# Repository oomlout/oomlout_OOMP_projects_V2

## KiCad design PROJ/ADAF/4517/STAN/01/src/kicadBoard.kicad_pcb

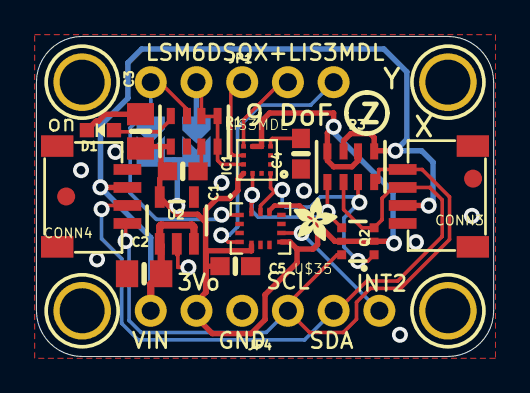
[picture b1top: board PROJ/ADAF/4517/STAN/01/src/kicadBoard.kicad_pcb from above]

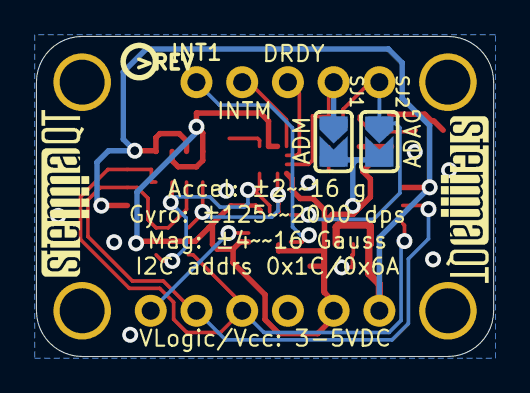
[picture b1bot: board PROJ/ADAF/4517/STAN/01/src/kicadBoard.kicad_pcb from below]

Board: 2 copper layers, 25.4 x 17.8 mm, 28 parts (5 on the bottom side), 15 nets.

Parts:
C1, C4: 0.1uF; 0603-NO
C2, C3: 10uF; 0805-NO
C5: 1uF; 0603-NO
CONN3, CONN4: STEMMA_I2C_QT; JST_SH4
D1: GREEN; CHIPLED_0603_NOOUTLINE
FID3, FID4: FIDUCIAL_1MM
IC1: LIS3MDL; LGA12_2X2MM
JP1: 1X05_ROUND_70
JP4: 1X06_ROUND_70
Q2: BSS138; SOT363
R1, R3: 10K; RESPACK_4X0603
SJ1, SJ2: SOLDERJUMPER_ARROW_NOPASTE
U2: AP2112K-3.3; SOT23-5
U$1, U$17, U$19, U$21: MOUNTINGHOLE2.5; MOUNTINGHOLE_2.5_PLATED
U$20: ADAFRUIT_2.5MM
U$25: PCBFEAT-REV-040
U$30, U$31: STEMMAQT
U$35: LSM6DSOX; LGA-14L

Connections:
3.3V: C1.1, C3.1, C5.1, IC1.5, IC1.6, IC1.10, JP4.2, Q2.2, Q2.5, R1.1, R3.2, R3.4, SJ1.2, SJ2.2, U2.5, U$35.5, U$35.8, U$35.12
ADAG: JP1.1, R1.7, SJ2.1, U$35.1
ADM: IC1.9, JP1.2, R1.4, R1.5, R1.6, SJ1.1
CAP: C4.1, IC1.4
DRDY: IC1.8, JP1.3
GND: C1.2, C2.2, C3.2, C4.2, C5.2, CONN3.1, CONN3.MT1, CONN3.MT2, CONN4.1, CONN4.MT1, CONN4.MT2, D1.C, IC1.2, IC1.3, IC1.12, JP4.3, R1.2, R1.3, U2.2, U$35.6, U$35.7
INT1: JP1.5, U$35.4
INT2: JP4.6, U$35.9
INTM: IC1.7, JP1.4
unnamed: D1.A, R1.8
SCL: CONN3.4, CONN4.4, JP4.4, Q2.6, R3.8
SCL_3V: IC1.1, Q2.1, R3.7, U$35.13
SDA: CONN3.3, CONN4.3, JP4.5, Q2.3, R3.6
SDA_3V: IC1.11, Q2.4, R3.5, U$35.14
VCC: C2.1, CONN3.2, CONN4.2, JP4.1, R3.1, R3.3, U2.1, U2.3

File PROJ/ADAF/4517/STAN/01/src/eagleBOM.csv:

"Part";"Value";"Device";"Package";"Description";"BOM";
"C1";"0.1uF";"CAP_CERAMIC0603_NO";"0603-NO";"Ceramic Capacitors";"";
"C2";"10uF";"CAP_CERAMIC0805-NOOUTLINE";"0805-NO";"Ceramic Capacitors";"";
"C3";"10uF";"CAP_CERAMIC0805-NOOUTLINE";"0805-NO";"Ceramic Capacitors";"";
"C4";"0.1uF";"CAP_CERAMIC0603_NO";"0603-NO";"Ceramic Capacitors";"";
"C5";"1uF";"CAP_CERAMIC0603_NO";"0603-NO";"Ceramic Capacitors";"";
"CONN3";"STEMMA_I2C_QT";"STEMMA_I2C_QT";"JST_SH4";"";"";
"CONN4";"STEMMA_I2C_QT";"STEMMA_I2C_QT";"JST_SH4";"";"";
"D1";"GREEN";"LED0603_NOOUTLINE";"CHIPLED_0603_NOOUTLINE";"LED";"";
"FID3";"FIDUCIAL_1MM";"FIDUCIAL_1MM";"FIDUCIAL_1MM";"Fiducial Alignment Points";"EXCLUDE";
"FID4";"FIDUCIAL_1MM";"FIDUCIAL_1MM";"FIDUCIAL_1MM";"Fiducial Alignment Points";"EXCLUDE";
"IC1";"LIS3MDL";"LIS3MDL";"LGA12_2X2MM";"Digital output magnetic sensor. ultra-low-power, high-performance 3-axis magnetometer";"";
"JP1";"";"HEADER-1X570MIL";"1X05_ROUND_70";"PIN HEADER";"";
"JP4";"";"HEADER-1X670MIL";"1X06_ROUND_70";"PIN HEADER";"";
"Q2";"BSS138";"MOSFET-N_DUAL";"SOT363";"Dual N-Channel MOSFET";"";
"R1";"10K";"RESISTOR_4PACK";"RESPACK_4X0603";"Resistor Packs (4 resistors)";"";
"R3";"10K";"RESISTOR_4PACK";"RESPACK_4X0603";"Resistor Packs (4 resistors)";"";
"SJ1";"";"SOLDERJUMPER";"SOLDERJUMPER_ARROW_NOPASTE";"SMD Solder JUMPER";"EXCLUDE";
"SJ2";"";"SOLDERJUMPER";"SOLDERJUMPER_ARROW_NOPASTE";"SMD Solder JUMPER";"EXCLUDE";
"U$1";"MOUNTINGHOLE2.5";"MOUNTINGHOLE2.5";"MOUNTINGHOLE_2.5_PLATED";"Mounting Hole";"EXCLUDE";
"U$17";"MOUNTINGHOLE2.5";"MOUNTINGHOLE2.5";"MOUNTINGHOLE_2.5_PLATED";"Mounting Hole";"EXCLUDE";
"U$19";"MOUNTINGHOLE2.5";"MOUNTINGHOLE2.5";"MOUNTINGHOLE_2.5_PLATED";"Mounting Hole";"EXCLUDE";
"U$21";"MOUNTINGHOLE2.5";"MOUNTINGHOLE2.5";"MOUNTINGHOLE_2.5_PLATED";"Mounting Hole";"EXCLUDE";
"U$35";"LSM6DSOX";"LSM6DSOX";"LGA-14L";"";"";
"U2";"AP2112K-3.3";"VREG_SOT23-5";"SOT23-5";"SOT23-5 Fixed Voltage Regulators";"";

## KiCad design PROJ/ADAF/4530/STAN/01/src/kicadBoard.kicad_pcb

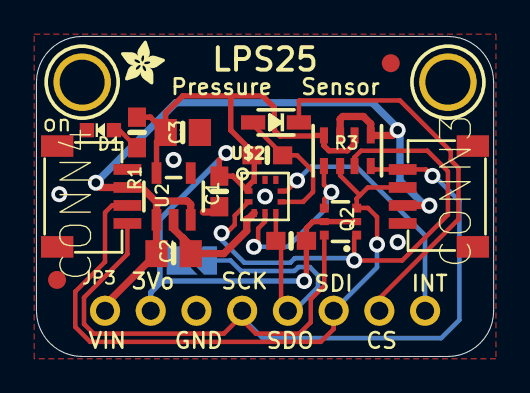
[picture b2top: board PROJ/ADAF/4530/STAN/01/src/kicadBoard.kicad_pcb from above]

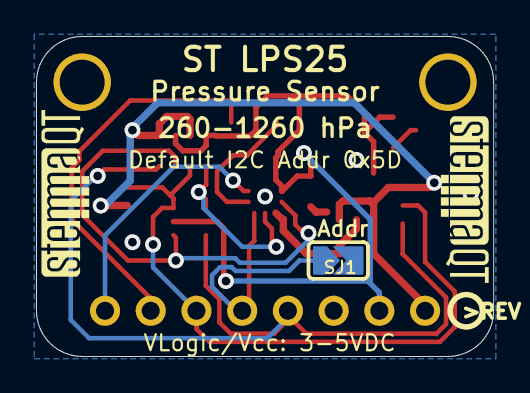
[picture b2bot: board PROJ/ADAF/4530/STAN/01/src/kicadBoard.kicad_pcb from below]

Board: 2 copper layers, 25.4 x 17.8 mm, 24 parts (4 on the bottom side), 12 nets.

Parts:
C1: 0.1uF; 0603-NO
C2, C3: 10uF; 0805-NO
CONN3, CONN4: STEMMA_I2C_QT; JST_SH4
D1: GREEN; CHIPLED_0603_NOOUTLINE
D2: 1N4148; SOD-323
FID3, FID4: FIDUCIAL_1MM
JP3: 1X08_ROUND
Q2: BSS138; SOT363
R1, R4, R5: 10K; 0603-NO
R3: 10K; RESPACK_4X0603
SJ1: SOLDERJUMPER_ARROW_NOPASTE
U2: AP2112K-3.3; SOT23-5
U$1, U$17: MOUNTINGHOLE2.5; MOUNTINGHOLE_2.5_PLATED
U$2: LPS2X_LPS25; HLGA-10L
U$4: ADAFRUIT_2.5MM
U$25: PCBFEAT-REV-040
U$30, U$31: STEMMAQT

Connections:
3.3V: C1.1, C3.1, JP3.2, Q2.2, Q2.5, R1.1, R3.2, R3.4, R4.2, R5.2, U2.5, U$2.1, U$2.10
CS: D2.C, JP3.7
CS_3V: D2.A, R5.1, U$2.6
GND: C1.2, C2.2, C3.2, CONN3.1, CONN4.1, D1.C, JP3.3, SJ1.2, U2.2, U$2.3, U$2.8, U$2.9
INT: JP3.8, U$2.7
unnamed: D1.A, R1.2
SCK/SCL: CONN3.4, CONN4.4, JP3.4, Q2.6, R3.8
SCK_3V: Q2.1, R3.7, U$2.2
SDI/SDA: CONN3.3, CONN4.3, JP3.6, Q2.3, R3.6
SDI_3V: Q2.4, R3.5, U$2.4
SDO/ADR: JP3.5, R4.1, SJ1.1, U$2.5
VCC: C2.1, CONN3.2, CONN4.2, JP3.1, R3.1, R3.3, U2.1, U2.3

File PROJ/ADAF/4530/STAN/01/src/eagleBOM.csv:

"Part";"Value";"Device";"Package";"Description";"BOM";
"C1";"0.1uF";"CAP_CERAMIC0603_NO";"0603-NO";"Ceramic Capacitors";"";
"C2";"10uF";"CAP_CERAMIC0805-NOOUTLINE";"0805-NO";"Ceramic Capacitors";"";
"C3";"10uF";"CAP_CERAMIC0805-NOOUTLINE";"0805-NO";"Ceramic Capacitors";"";
"CONN3";"STEMMA_I2C_QT";"STEMMA_I2C_QT";"JST_SH4";"";"";
"CONN4";"STEMMA_I2C_QT";"STEMMA_I2C_QT";"JST_SH4";"";"";
"D1";"GREEN";"LED0603_NOOUTLINE";"CHIPLED_0603_NOOUTLINE";"LED";"";
"D2";"1N4148";"DIODESOD-323";"SOD-323";"Diode";"";
"FID3";"FIDUCIAL_1MM";"FIDUCIAL_1MM";"FIDUCIAL_1MM";"Fiducial Alignment Points";"EXCLUDE";
"FID4";"FIDUCIAL_1MM";"FIDUCIAL_1MM";"FIDUCIAL_1MM";"Fiducial Alignment Points";"EXCLUDE";
"JP3";"";"HEADER-1X8ROUND";"1X08_ROUND";"PIN HEADER";"";
"Q2";"BSS138";"MOSFET-N_DUAL";"SOT363";"Dual N-Channel MOSFET";"";
"R1";"10K";"RESISTOR_0603_NOOUT";"0603-NO";"Resistors";"";
"R3";"10K";"RESISTOR_4PACK";"RESPACK_4X0603";"Resistor Packs (4 resistors)";"";
"R4";"10K";"RESISTOR_0603_NOOUT";"0603-NO";"Resistors";"";
"R5";"10K";"RESISTOR_0603_NOOUT";"0603-NO";"Resistors";"";
"SJ1";"";"SOLDERJUMPER";"SOLDERJUMPER_ARROW_NOPASTE";"SMD Solder JUMPER";"EXCLUDE";
"U$1";"MOUNTINGHOLE2.5";"MOUNTINGHOLE2.5";"MOUNTINGHOLE_2.5_PLATED";"Mounting Hole";"EXCLUDE";
"U$2";"LPS2X_LPS25";"LPS2X_LPS25";"HLGA-10L";"";"";
"U$17";"MOUNTINGHOLE2.5";"MOUNTINGHOLE2.5";"MOUNTINGHOLE_2.5_PLATED";"Mounting Hole";"EXCLUDE";
"U2";"AP2112K-3.3";"VREG_SOT23-5";"SOT23-5";"SOT23-5 Fixed Voltage Regulators";"";

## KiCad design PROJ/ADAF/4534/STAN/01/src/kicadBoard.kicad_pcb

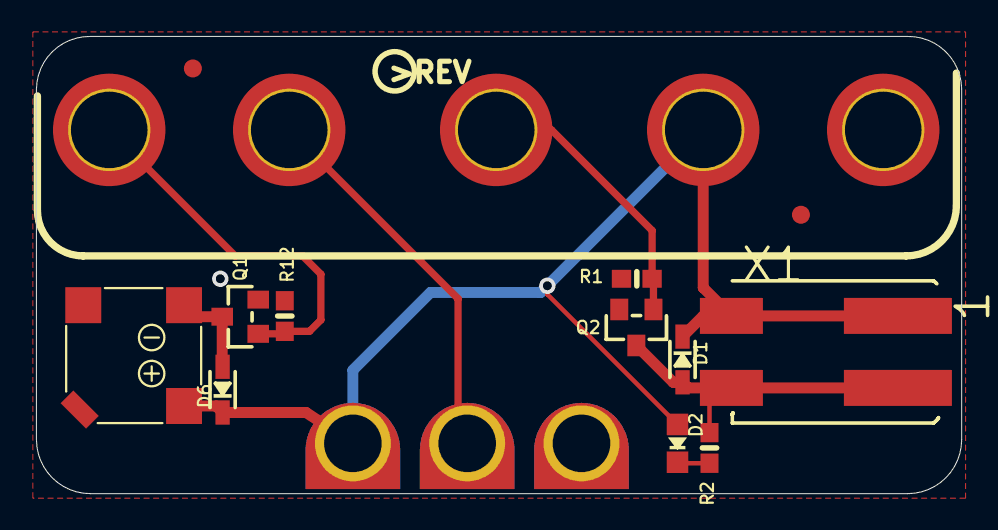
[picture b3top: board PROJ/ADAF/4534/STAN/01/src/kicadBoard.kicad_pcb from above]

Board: 2 copper layers, 51.4 x 25.4 mm, 19 parts (1 on the bottom side), 8 nets.

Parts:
D1, D6: 1N4148; SOD-323
D2: red; CHIPLED_0805_NOOUTLINE
FID1, FID2: FIDUCIAL_1MM
MB2: MICROBIT_5PIN; MICROBIT_5SMTNUT
Q1, Q2: BSS138; SOT23-WIDE
R1, R12: 10K; 0603-NO
R2: 1K; 0603-NO
SP1: SPEAKER_7.5MM; BUZZER_SMT_7.5MM
TP1, TP2, TP3: SEWTAPPCB_ALLIGATOR; PCB_ALLI
U$4: BONSAI_BOT
U$5: BONSAI_TOP
U$10: PCBFEAT-REV-056
X1: 2060-402/998-404; P-2060-402_998-404

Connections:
3.3V: D1.C, D2.A, D6.C, MB2.3V, SP1.+, TP1.P$1, X1.L1.1, X1.L1.2
GND: MB2.GND, Q1.2, Q2.2, R1.2, R12.2, TP3.P$1
unnamed: D1.A, Q2.3, R2.1, X1.L2.1, X1.L2.2
unnamed: D2.C, R2.2
unnamed: D6.A, Q1.3, SP1.-
P0: MB2.P0, Q1.1, R12.1
P1: MB2.P1, TP2.P$1
P2: MB2.P2, Q2.1, R1.1

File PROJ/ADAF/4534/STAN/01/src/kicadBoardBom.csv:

"Id";"Designator";"Package";"Quantity";"Designation";"Supplier and ref";
1;"D2";"CHIPLED_0805_NOOUTLINE";1;"red";;;
2;"FID1,FID2";"FIDUCIAL_1MM";2;"FIDUCIAL_1MM";;;
3;"Q2,Q1";"SOT23-WIDE";2;"BSS138";;;
4;"SP1";"BUZZER_SMT_7.5MM";1;"SPEAKER_7.5MM";;;
5;"TP3,TP1,TP2";"PCB_ALLI";3;"SEWTAPPCB_ALLIGATOR";;;
6;"R1,R12";"0603-NO";2;"10K";;;
7;"U$5";"BONSAI_TOP";1;"";;;
8;"D1,D6";"SOD-323";2;"1N4148";;;
9;"MB2";"MICROBIT_5SMTNUT";1;"MICROBIT_5PIN";;;
10;"X1";"P-2060-402_998-404";1;"2060-402/998-404";;;
11;"R2";"0603-NO";1;"1K";;;
12;"U$10";"PCBFEAT-REV-056";1;"";;;
13;"U$4";"BONSAI_BOT";1;"";;;

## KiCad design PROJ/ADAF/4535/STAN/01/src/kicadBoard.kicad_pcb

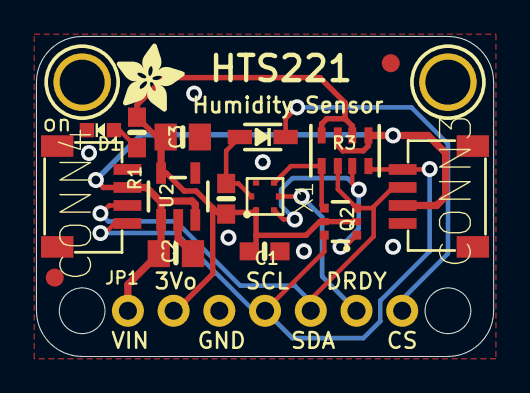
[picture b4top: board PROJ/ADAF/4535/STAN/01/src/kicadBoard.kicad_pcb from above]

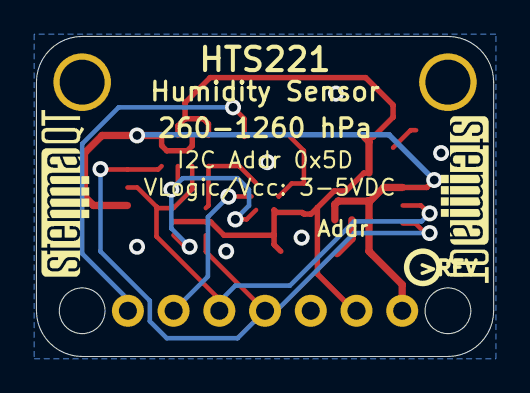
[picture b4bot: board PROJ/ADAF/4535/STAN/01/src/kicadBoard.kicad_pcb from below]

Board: 2 copper layers, 25.4 x 17.8 mm, 24 parts (3 on the bottom side), 11 nets.

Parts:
@HOLE0, @HOLE1: (no value)
C1: 0.1uF; 0603-NO
C2, C3: 10uF; 0805-NO
CONN3, CONN4: STEMMA_I2C_QT; JST_SH4
D1: GREEN; CHIPLED_0603_NOOUTLINE
D2: 1N4148; SOD-323
FID3, FID4: FIDUCIAL_1MM
JP1: 1X07_ROUND_70
Q2: BSS138; SOT363
R1, R5: 10K; 0603-NO
R3: 10K; RESPACK_4X0603
U2: AP2112K-3.3; SOT23-5
U$1, U$17: MOUNTINGHOLE2.5; MOUNTINGHOLE_2.5_PLATED
U$4: ADAFRUIT_3.5MM
U$25: PCBFEAT-REV-040
U$30, U$31: STEMMAQT
X1: HTS221; HLGA-6L

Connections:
3.3V: C1.1, C3.1, JP1.2, Q2.2, Q2.5, R1.1, R3.2, R3.4, R5.2, U2.5, X1.1
CS: D2.C, JP1.7
CS_3V: D2.A, R5.1, X1.6
DRDY: JP1.6, X1.3
GND: C1.2, C2.2, C3.2, CONN3.1, CONN4.1, D1.C, JP1.3, U2.2, X1.5
unnamed: D1.A, R1.2
SCL: CONN3.4, CONN4.4, JP1.4, Q2.6, R3.8
SCL_3V: Q2.1, R3.7, X1.2
SDA: CONN3.3, CONN4.3, JP1.5, Q2.3, R3.6
SDA_3V: Q2.4, R3.5, X1.4
VCC: C2.1, CONN3.2, CONN4.2, JP1.1, R3.1, R3.3, U2.1, U2.3

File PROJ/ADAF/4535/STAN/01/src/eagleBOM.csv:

"Part";"Value";"Device";"Package";"Description";"BOM";
"C1";"0.1uF";"CAP_CERAMIC0603_NO";"0603-NO";"Ceramic Capacitors";"";
"C2";"10uF";"CAP_CERAMIC0805-NOOUTLINE";"0805-NO";"Ceramic Capacitors";"";
"C3";"10uF";"CAP_CERAMIC0805-NOOUTLINE";"0805-NO";"Ceramic Capacitors";"";
"CONN3";"STEMMA_I2C_QT";"STEMMA_I2C_QT";"JST_SH4";"";"";
"CONN4";"STEMMA_I2C_QT";"STEMMA_I2C_QT";"JST_SH4";"";"";
"D1";"GREEN";"LED0603_NOOUTLINE";"CHIPLED_0603_NOOUTLINE";"LED";"";
"D2";"1N4148";"DIODESOD-323";"SOD-323";"Diode";"";
"FID3";"FIDUCIAL_1MM";"FIDUCIAL_1MM";"FIDUCIAL_1MM";"Fiducial Alignment Points";"EXCLUDE";
"FID4";"FIDUCIAL_1MM";"FIDUCIAL_1MM";"FIDUCIAL_1MM";"Fiducial Alignment Points";"EXCLUDE";
"JP1";"";"HEADER-1X770MIL";"1X07_ROUND_70";"PIN HEADER";"";
"Q2";"BSS138";"MOSFET-N_DUAL";"SOT363";"Dual N-Channel MOSFET";"";
"R1";"10K";"RESISTOR_0603_NOOUT";"0603-NO";"Resistors";"";
"R3";"10K";"RESISTOR_4PACK";"RESPACK_4X0603";"Resistor Packs (4 resistors)";"";
"R5";"10K";"RESISTOR_0603_NOOUT";"0603-NO";"Resistors";"";
"U$1";"MOUNTINGHOLE2.5";"MOUNTINGHOLE2.5";"MOUNTINGHOLE_2.5_PLATED";"Mounting Hole";"EXCLUDE";
"U$17";"MOUNTINGHOLE2.5";"MOUNTINGHOLE2.5";"MOUNTINGHOLE_2.5_PLATED";"Mounting Hole";"EXCLUDE";
"U2";"AP2112K-3.3";"VREG_SOT23-5";"SOT23-5";"SOT23-5 Fixed Voltage Regulators";"";
"X1";"HTS221";"HTS221";"HLGA-6L";"";"";

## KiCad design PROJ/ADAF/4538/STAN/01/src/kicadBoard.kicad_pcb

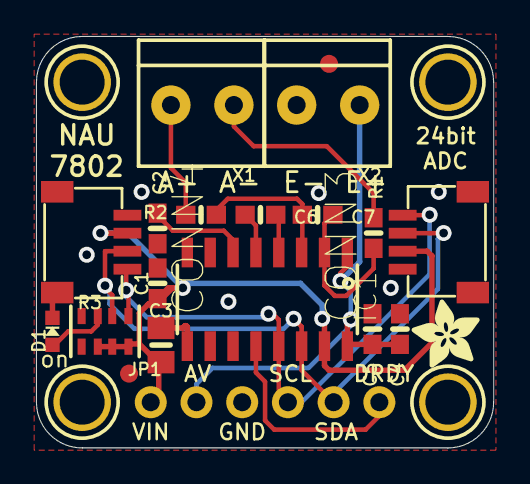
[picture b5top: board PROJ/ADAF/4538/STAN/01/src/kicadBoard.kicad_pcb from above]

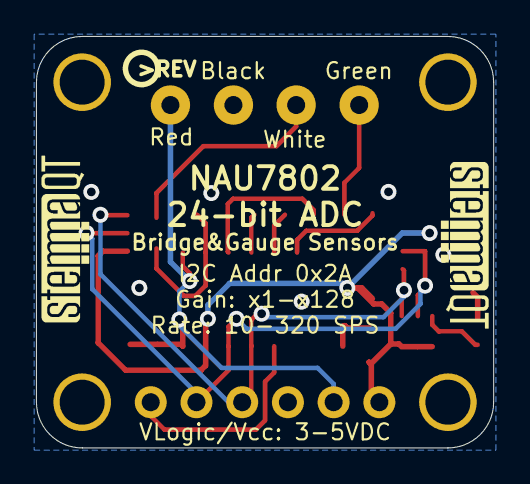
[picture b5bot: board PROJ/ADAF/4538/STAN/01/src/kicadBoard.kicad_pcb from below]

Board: 2 copper layers, 25.4 x 22.9 mm, 27 parts (3 on the bottom side), 14 nets.

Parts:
C1, C2, C4, C7: 0.1uF; 0603-NO
C3: 10uF; 0805-NO
C5: 1uF; 0603-NO
C6: 470pF; 0603-NO
CONN3, CONN4: STEMMA_I2C_QT; JST_SH4
D1: GREEN; CHIPLED_0603_NOOUTLINE
FID3, FID4: FIDUCIAL_1MM
IC1: NAU7802; SOIC16_NARROW
JP1: 1X06_ROUND_70
R1, R2: 51; 0603-NO
R3: 10K; RESPACK_4X0603
U$1, U$17, U$19, U$21: MOUNTINGHOLE2.5; MOUNTINGHOLE_2.5_PLATED
U$22: ADAFRUIT_3.5MM
U$25: PCBFEAT-REV-040
U$30, U$31: STEMMAQT
X1, X2: 3.5mm; TERMBLOCK_1X2-3.5MM

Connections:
A+: R2.2, X1.1
A-: R1.2, X1.2
AVDD: C4.2, C5.2, IC1.1, IC1.16, JP1.2, X2.2
DRDY: IC1.12, JP1.6
GND: C1.2, C2.1, C3.2, C4.1, C5.1, CONN3.1, CONN3.MT1, CONN3.MT2, CONN4.1, CONN4.MT1, CONN4.MT2, D1.C, IC1.7, IC1.8, IC1.9, JP1.3, X2.1
unnamed: D1.A, R3.7
unnamed: C2.2, IC1.6
unnamed: C6.2, IC1.4
unnamed: C6.1, IC1.5
unnamed: C7.1, IC1.3, R2.1
unnamed: C7.2, IC1.2, R1.1
SCL: CONN3.4, CONN4.4, IC1.13, JP1.4, R3.5
SDA: CONN3.3, CONN4.3, IC1.14, JP1.5, R3.6
VCC: C1.1, C3.1, CONN3.2, CONN4.2, IC1.15, JP1.1, R3.2, R3.3, R3.4

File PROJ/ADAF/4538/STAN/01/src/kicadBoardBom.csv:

"Id";"Designator";"Package";"Quantity";"Designation";"Supplier and ref";
1;"C6";"0603-NO";1;"470pF";;;
2;"U$19,U$21,U$17,U$1";"MOUNTINGHOLE_2.5_PLATED";4;"MOUNTINGHOLE2.5";;;
3;"JP1";"1X06_ROUND_70";1;"";;;
4;"U$22";"ADAFRUIT_3.5MM";1;"";;;
5;"FID3,FID4";"FIDUCIAL_1MM";2;"FIDUCIAL_1MM";;;
6;"CONN3,CONN4";"JST_SH4";2;"STEMMA_I2C_QT";;;
7;"D1";"CHIPLED_0603_NOOUTLINE";1;"GREEN";;;
8;"C2,C4,C1,C7";"0603-NO";4;"0.1uF";;;
9;"C5";"0603-NO";1;"1uF";;;
10;"X1,X2";"TERMBLOCK_1X2-3.5MM";2;"3.5mm";;;
11;"R3";"RESPACK_4X0603";1;"10K";;;
12;"IC1";"SOIC16_NARROW";1;"NAU7802";;;
13;"R1,R2";"0603-NO";2;"51";;;
14;"C3";"0805-NO";1;"10uF";;;
15;"U$30,U$31";"STEMMAQT";2;"";;;
16;"U$25";"PCBFEAT-REV-040";1;"";;;

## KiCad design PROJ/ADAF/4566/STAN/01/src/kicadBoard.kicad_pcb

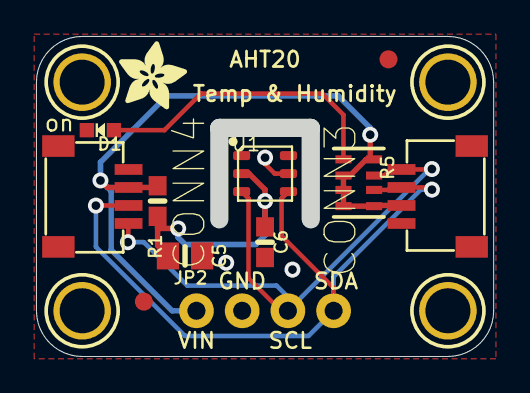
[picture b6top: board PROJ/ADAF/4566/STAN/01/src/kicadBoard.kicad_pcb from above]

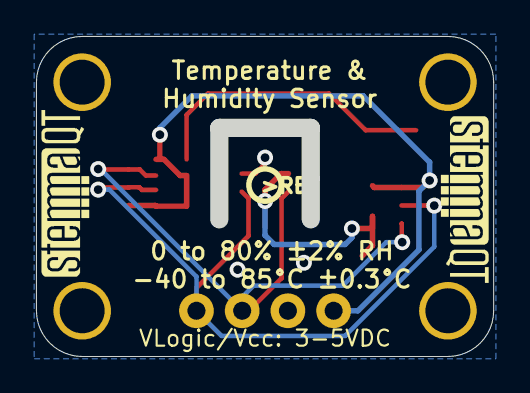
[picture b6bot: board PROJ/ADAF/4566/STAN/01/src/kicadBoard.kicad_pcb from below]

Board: 2 copper layers, 25.4 x 17.8 mm, 19 parts (3 on the bottom side), 6 nets.

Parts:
C5: 10uF; 0805-NO
C6: 0.1uF; 0603-NO
CONN3, CONN4: STEMMA_I2C_QT; JST_SH4
D1: GREEN; CHIPLED_0603_NOOUTLINE
FID3, FID4: FIDUCIAL_1MM
JP2: 1X04_ROUND_76
R1: 220; 0603-NO
R5: 10K; RESPACK_4X0603
U1: AHT20; SNR6-1.0-3X3X1MM
U$19, U$20, U$22, U$25: MOUNTINGHOLE2.5; MOUNTINGHOLE_2.5_PLATED
U$28: ADAFRUIT_3.5MM
U$29: PCBFEAT-REV-040
U$30, U$31: STEMMAQT

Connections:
GND: C5.2, C6.2, CONN3.1, CONN3.MT1, CONN3.MT2, CONN4.1, CONN4.MT1, CONN4.MT2, D1.C, JP2.2, U1.5
unnamed: D1.A, R5.1
SCL: CONN3.4, CONN4.4, JP2.3, R5.7, U1.3
SDA: CONN3.3, CONN4.3, JP2.4, R5.6, U1.4
VCC: CONN3.2, CONN4.2, JP2.1, R1.1, R5.2, R5.3, R5.4, R5.5, R5.8
VDD: C5.1, C6.1, R1.2, U1.2

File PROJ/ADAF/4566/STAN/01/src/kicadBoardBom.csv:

"Id";"Designator";"Package";"Quantity";"Designation";"Supplier and ref";
1;"D1";"CHIPLED_0603_NOOUTLINE";1;"GREEN";;;
2;"JP2";"1X04_ROUND_76";1;"";;;
3;"C6";"0603-NO";1;"0.1uF";;;
4;"CONN3,CONN4";"JST_SH4";2;"STEMMA_I2C_QT";;;
5;"U$22,U$20,U$19,U$25";"MOUNTINGHOLE_2.5_PLATED";4;"MOUNTINGHOLE2.5";;;
6;"R5";"RESPACK_4X0603";1;"10K";;;
7;"FID3,FID4";"FIDUCIAL_1MM";2;"FIDUCIAL_1MM";;;
8;"R1";"0603-NO";1;"220";;;
9;"C5";"0805-NO";1;"10uF";;;
10;"U1";"SNR6-1.0-3X3X1MM";1;"AHT20";;;
11;"U$28";"ADAFRUIT_3.5MM";1;"";;;
12;"U$29";"PCBFEAT-REV-040";1;"";;;
13;"U$31,U$30";"STEMMAQT";2;"";;;

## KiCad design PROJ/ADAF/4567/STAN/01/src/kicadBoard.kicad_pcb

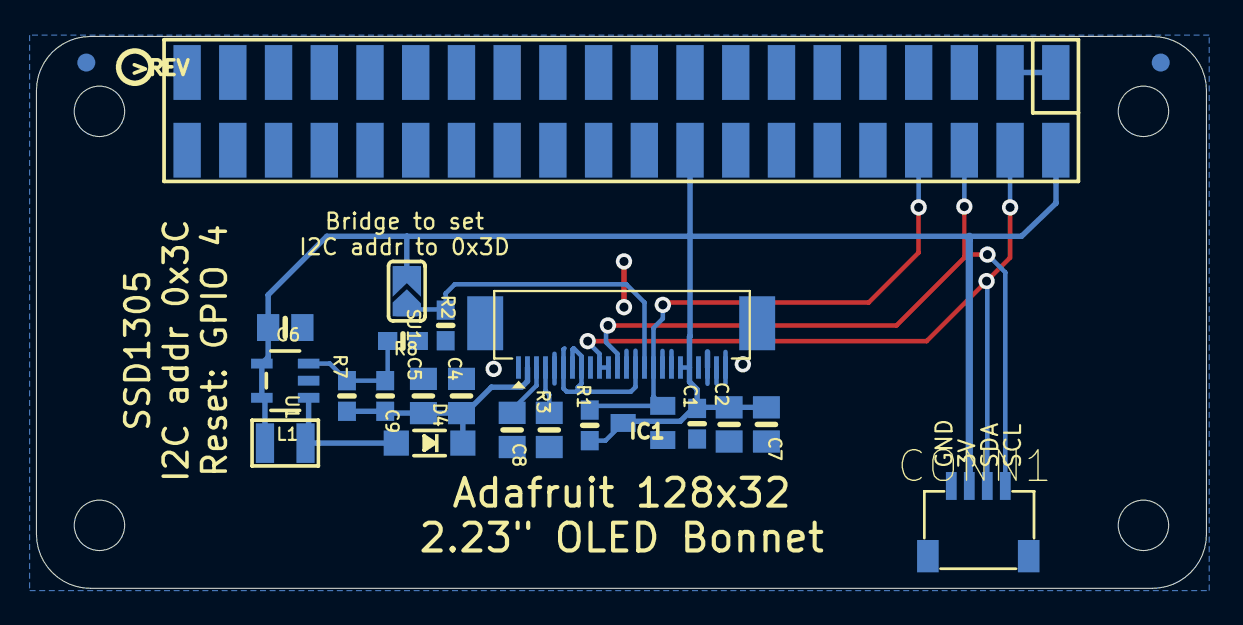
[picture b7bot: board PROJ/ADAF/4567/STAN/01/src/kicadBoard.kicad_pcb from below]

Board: 2 copper layers, 65.0 x 30.7 mm, 23 parts (20 on the bottom side), 12 nets.

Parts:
C1, C9: 0.1uF; 0603-NO
C2, C4, C5, C6, C8: 10uF; 0805-NO
C7: 2.2uF; 0805-NO
CONN1: STEMMA_I2C_QT; JST_SH4
D4: MBR120; SOD-123
IC1: APX803S-29SA; SOT23
L1: 10uH; INDUCTOR_1007
R1, R2, R8: 10K; 0603-NO
R3: 910K; 0805-NO
R7: 100K; 0603-NO
RPI1: RASPBERRYPI_BPLUS_BONNETSMT; PI_BONNET_SMT
SJ1: SOLDERJUMPER_ARROW_NOPASTE
U1: FAN5331; SOT23-5
U$2: PCBFEAT-REV-040
U$11: STEMMAQT
U$33: 2.23_INCH_OLEDBOTTOM_CONTACT_24_PIN_OLED; 2.23OLED_BOTTOM_CONTACT

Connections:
3.3V: C1.1, C2.1, C6.2, C7.2, CONN1.2, IC1.3, L1.P$1, R1.2, RPI1.1, RPI1.17, SJ1.2, U1.4, U1.5, U$33.5, U$33.6
5.0V: RPI1.2, RPI1.4
12V: C4.2, C5.2, C9.1, D4.C, R7.2, U$33.23
GND: C1.2, C2.2, C4.1, C5.1, C6.1, C7.1, C8.1, CONN1.1, IC1.1, R2.1, R3.1, R8.1, RPI1.6, RPI1.9, RPI1.14, RPI1.20, RPI1.25, RPI1.30, RPI1.34, RPI1.39, U1.2, U$33.1, U$33.2, U$33.3, U$33.7, U$33.8, U$33.11, U$33.12, U$33.16, U$33.17, U$33.18, U$33.19, U$33.20, U$33.24, U$33.SPRT1, U$33.SPRT2
unnamed: R3.2, U$33.21
unnamed: D4.A, L1.P$2, U1.1
unnamed: C9.2, R7.1, R8.2, U1.3
unnamed: C8.2, U$33.22
RST: IC1.2, R1.1, RPI1.7, U$33.9
SA0: R2.2, SJ1.1, U$33.10
SCL: CONN1.4, RPI1.5, U$33.13
SDA: CONN1.3, RPI1.3, U$33.14, U$33.15

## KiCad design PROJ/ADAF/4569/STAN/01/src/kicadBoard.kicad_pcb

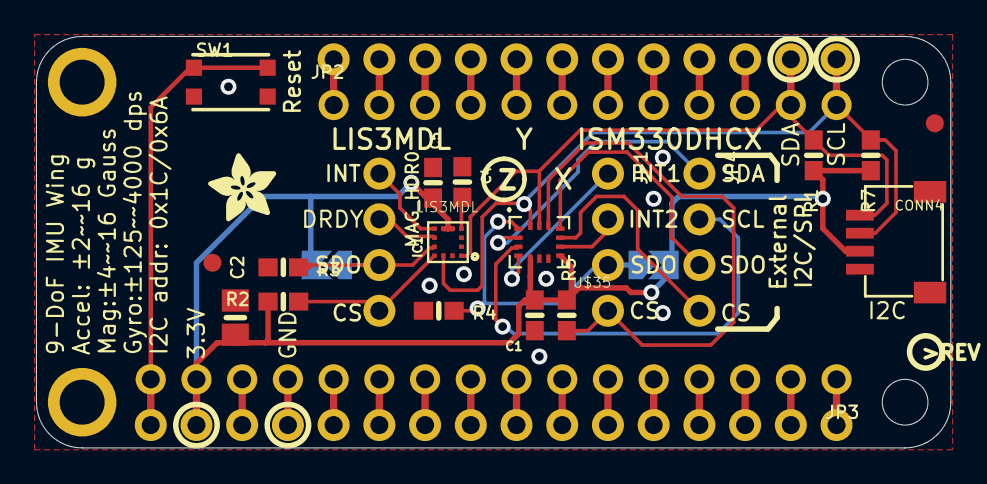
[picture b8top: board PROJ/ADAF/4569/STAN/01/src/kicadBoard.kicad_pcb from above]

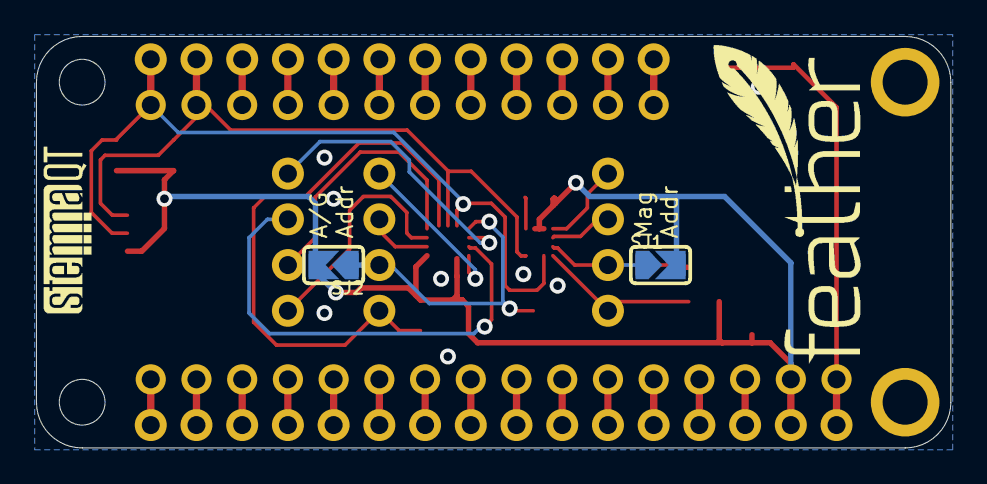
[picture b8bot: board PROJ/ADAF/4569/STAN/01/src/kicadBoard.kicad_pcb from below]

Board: 2 copper layers, 50.8 x 22.9 mm, 28 parts (4 on the bottom side), 41 nets.

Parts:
C1, C4: 0.1uF; 0603-NO
C2: 10uF; 0805-NO
C5: 1uF; 0603-NO
CONN4: STEMMA_I2C_QT; JST_SH4
FID1, FID2: FIDUCIAL_1MM
IC1: LIS3MDL; LGA12_2X2MM
JP1, JP4: 1X04_ROUND
JP2: 1X12_ROUND
JP3: 1X16_ROUND
MAG_HDR0: 1X04_ROUND
MS1: FEATHERWING
R1, R2, R3, R4, R5, R7: 10K; 0603-NO
SJ1, SJ2: SOLDERJUMPER_ARROW_NOPASTE
SW1: KMR2; BTN_KMR2_4.6X2.8
U$13: FEATHERLOGO_MED
U$31: STEMMAQT
U$35: LSM6DSOX; LGA-14L
U$50: ADAFRUIT_3.5MM
U$51: PCBFEAT-REV-040

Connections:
3.3V: C1.1, C2.1, C5.1, CONN4.2, IC1.5, IC1.6, JP3.15, MS1.2, R1.2, R2.2, R5.2, R7.2, SJ1.2, SJ2.2, U$35.5, U$35.8
A: JP3.12, MS1.5
AD_AG: JP1.3, R4.2, SJ2.1, U$35.1
AD_M: IC1.9, MAG_HDR0.3, R3.2, SJ1.1
AREF: JP3.14, MS1.3
B: JP3.11, MS1.6
C: JP3.10, MS1.7
CAP: C4.1, IC1.4
CS_AG: JP1.4, R5.1, U$35.12
CS_M: IC1.10, MAG_HDR0.4, R2.1
D: JP3.9, MS1.8
DRDY: IC1.8, MAG_HDR0.2
E: JP3.8, MS1.9
EN: JP2.2, MS1.27
F: JP3.7, MS1.10
G: JP3.1, MS1.16
GND: C1.2, C2.2, C4.2, C5.2, CONN4.1, CONN4.MT1, CONN4.MT2, IC1.2, IC1.3, IC1.12, JP3.13, MS1.4, R3.1, R4.1, SW1.B, SW1.B', U$35.6, U$35.7
H: JP2.10, MS1.19
I: JP2.9, MS1.20
INT1: JP1.1, U$35.4
INT2: JP1.2, U$35.9
INTM: IC1.7, MAG_HDR0.1
J: JP2.8, MS1.21
K: JP2.7, MS1.22
L: JP2.6, MS1.23
M: JP2.5, MS1.24
MISO: JP3.4, MS1.13
MOSI: JP3.5, MS1.12
N: JP2.4, MS1.25
OCS_EX: JP4.4, U$35.10
RESET: JP3.16, MS1.1, SW1.A, SW1.A'
RX: JP3.3, MS1.14
SCK: JP3.6, MS1.11
SCL: CONN4.4, IC1.1, JP2.11, MS1.18, R1.1, U$35.13
SCL_EX: JP4.2, U$35.3
SDA: CONN4.3, IC1.11, JP2.12, MS1.17, R7.1, U$35.14
SDA_EX: JP4.1, U$35.2
SDO_EX: JP4.3, U$35.11
TX: JP3.2, MS1.15
USB: JP2.3, MS1.26
VBAT: JP2.1, MS1.28
